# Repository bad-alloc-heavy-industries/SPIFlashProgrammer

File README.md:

# SPI Flash Programmer

After a complete rewrite and re-hash of the original ideal having had it proove itself, a PCB and tightly integrated yet simple to use firmware is the name of the game.

SPIFlashProgrammer is a small but capable board housing a Texas Instruments Tiva-C series ARM microprocessor, two Flash devices for use in a production environment to allow one board to program up to two different target devices on a production line, and USB for power and connecting to a host machine.

When connected to a host, the USB connectivity and `flashprog` utility come together to form a sleak programming experience, allowing the tool to be used in a "set and forget" manner for test and debug of bitstreams and firmware.

## Flash chip support

The firmware targets 25 series memory devices such as the M25P16, W25Q80BV, and AT25SF641.

## Build and installation

Building requires a small number of prerequsites and dependencies:

* [Meson](https://meson.build)
* [Ninja](https://ninja-build.org)
* A modern arm-none-eabi GCC such as the [GNU ARM Embedded Toolchain](https://developer.arm.com/tools-and-software/open-source-software/developer-tools/gnu-toolchain/gnu-rm)
	or any distro or custom build GCC capable of targeting ARMv7 via C++17

To build the firmware and host software, run

```Bash
meson build --cross-file=cross-files/arm-none-eabi.meson
ninja -C build
```

You may then use the results in-place, or install the host software with `ninja -C build install`.

Programming the firmware onto a newly minted board can be achived via any JTAG adapter that can talk TI ICDI.
We use the awesome [Black Magic Probe](https://github.com/blacksphere/blackmagic) with the toolchain GDB.

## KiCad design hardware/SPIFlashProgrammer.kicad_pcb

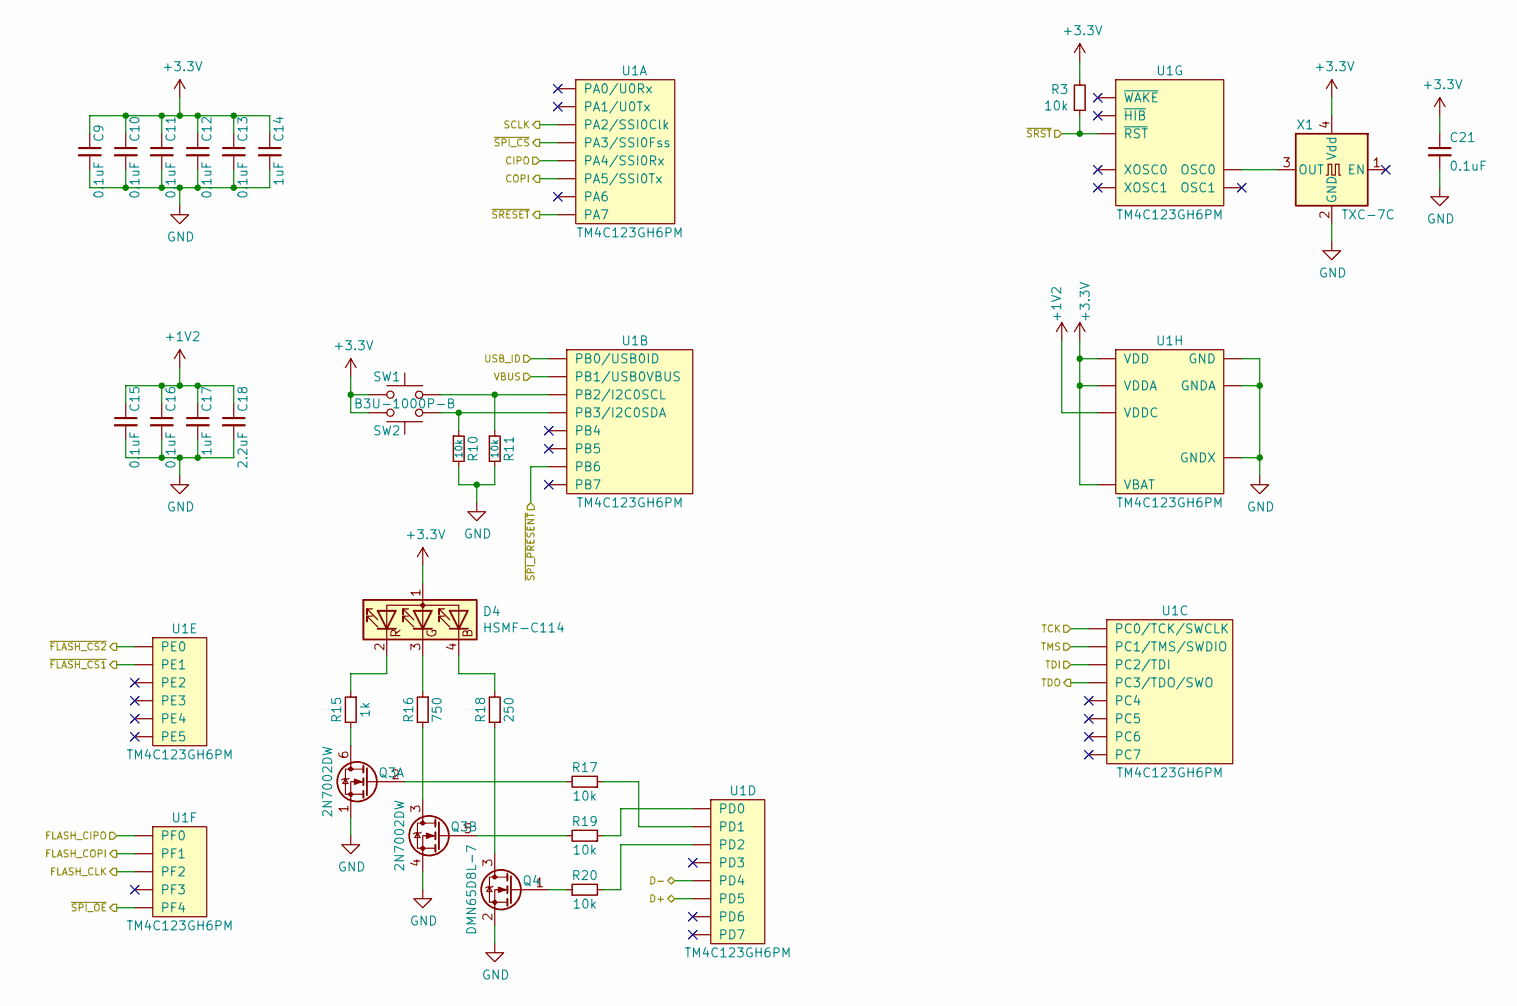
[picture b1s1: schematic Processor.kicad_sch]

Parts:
C9, C10, C11, C12, C13, C15, C16, C21: 0.1uF; C0603; MPN MC0603B104J250CT
C14, C17: 1uF; C0603; MPN MC0603B105K160CT
C18: 2.2uF; C0603; MPN C1608X5R1C225K080AB
D4: HSMF-C114; LED0606; MPN HSMF-C114
Q3: 2N7002DW; SOT-363_SC-70-6; MPN 2N7002DW
Q4: DMN65D8L-7; SOT-23; MPN DMN65D8L-7
R3, R10, R11, R17, R19, R20: 10k; R0603; MPN MC0063W0603110K
R15: 1k; R0603; MPN MC0063W0603110K
R16: 750; R0603; MPN MC0063W0603110K
R18: 250; R0603; MPN MC0063W0603110K
SW1, SW2: B3U-1000P-B; MPN B3U-1000P-B
U1: TM4C123GH6PM; QFP-64_10.2x10.2_Pitch0.5mm; MPN TM4C123GH6PM
X1: TXC-7C; SMD3225; MPN MCSJK-3N-25.00-3.3-50-B

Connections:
+1V2: C15.1, C16.1, C17.1, C18.1, U1.25 (VDDC), U1.56 (VDDC)
+3V3: C9.1, C10.1, C11.1, C12.1, C13.1, C14.1, C21.1, D4.1 (A), R3.2, SW1.1, SW2.1, U1.2 (VDDA), U1.11 (VDD), U1.26 (VDD), U1.37 (VBAT), U1.42 (VDD), U1.54 (VDD), X1.4 (Vdd); also elsewhere on the board
/Connectors/CIPO: U1.21 (PA4/SSI0Rx); also elsewhere on the board
/Connectors/COPI: U1.22 (PA5/SSI0Tx); also elsewhere on the board
/Connectors/D+: U1.44 (PD5); also elsewhere on the board
/Connectors/D-: U1.43 (PD4); also elsewhere on the board
/Connectors/SCLK: U1.19 (PA2/SSI0Clk); also elsewhere on the board
/Connectors/TCK: U1.52 (PC0/TCK/SWCLK); also elsewhere on the board
/Connectors/TDI: U1.50 (PC2/TDI); also elsewhere on the board
/Connectors/TDO: U1.49 (PC3/TDO/SWO); also elsewhere on the board
/Connectors/TMS: U1.51 (PC1/TMS/SWDIO); also elsewhere on the board
/Connectors/USB_ID: U1.45 (PB0/USB0ID); also elsewhere on the board
/Connectors/VBUS: U1.46 (PB1/USB0VBUS); also elsewhere on the board
/Connectors/~SPI_CS: U1.20 (PA3/SSI0Fss); also elsewhere on the board
/Connectors/~SPI_OE: U1.5 (PF4); also elsewhere on the board
/Connectors/~SPI_PRESENT: U1.1 (PB6); also elsewhere on the board
/Connectors/~SRESET: U1.24 (PA7); also elsewhere on the board
/Connectors/~SRST: R3.1, U1.38 (~RST); also elsewhere on the board
/Onboard Flash/CIPO: U1.28 (PF0); also elsewhere on the board
/Onboard Flash/COPI: U1.29 (PF1); also elsewhere on the board
/Onboard Flash/SCK: U1.30 (PF2); also elsewhere on the board
/Onboard Flash/~CS1: U1.8 (PE1); also elsewhere on the board
/Onboard Flash/~CS2: U1.9 (PE0); also elsewhere on the board
GND: C9.2, C10.2, C11.2, C12.2, C13.2, C14.2, C15.2, C16.2, C17.2, C18.2, C21.2, Q3.1 (S), Q3.4 (S), Q4.2 (S), R10.2, R11.2, U1.3 (GNDA), U1.12 (GND), U1.27 (GND), U1.35 (GNDX), U1.39 (GND), U1.55 (GND), X1.2 (GND); also elsewhere on the board
unnamed: D4.2 (RK), R15.1
unnamed: D4.3 (GK), R16.1
unnamed: D4.4 (BK), R18.2
unnamed: Q3.2 (G), R17.2
unnamed: Q3.3 (D), R16.2
unnamed: Q3.5 (G), R19.2
unnamed: Q3.6 (D), R15.2
unnamed: Q4.1 (G), R20.1
unnamed: Q4.3 (D), R18.1
unnamed: R10.1, SW2.2, U1.48 (PB3/I2C0SDA)
unnamed: R11.1, SW1.2, U1.47 (PB2/I2C0SCL)
unnamed: R17.1, U1.62 (PD1)
unnamed: R19.1, U1.61 (PD0)
unnamed: R20.2, U1.63 (PD2)
unnamed: U1.40 (OSC0), X1.3 (OUT)

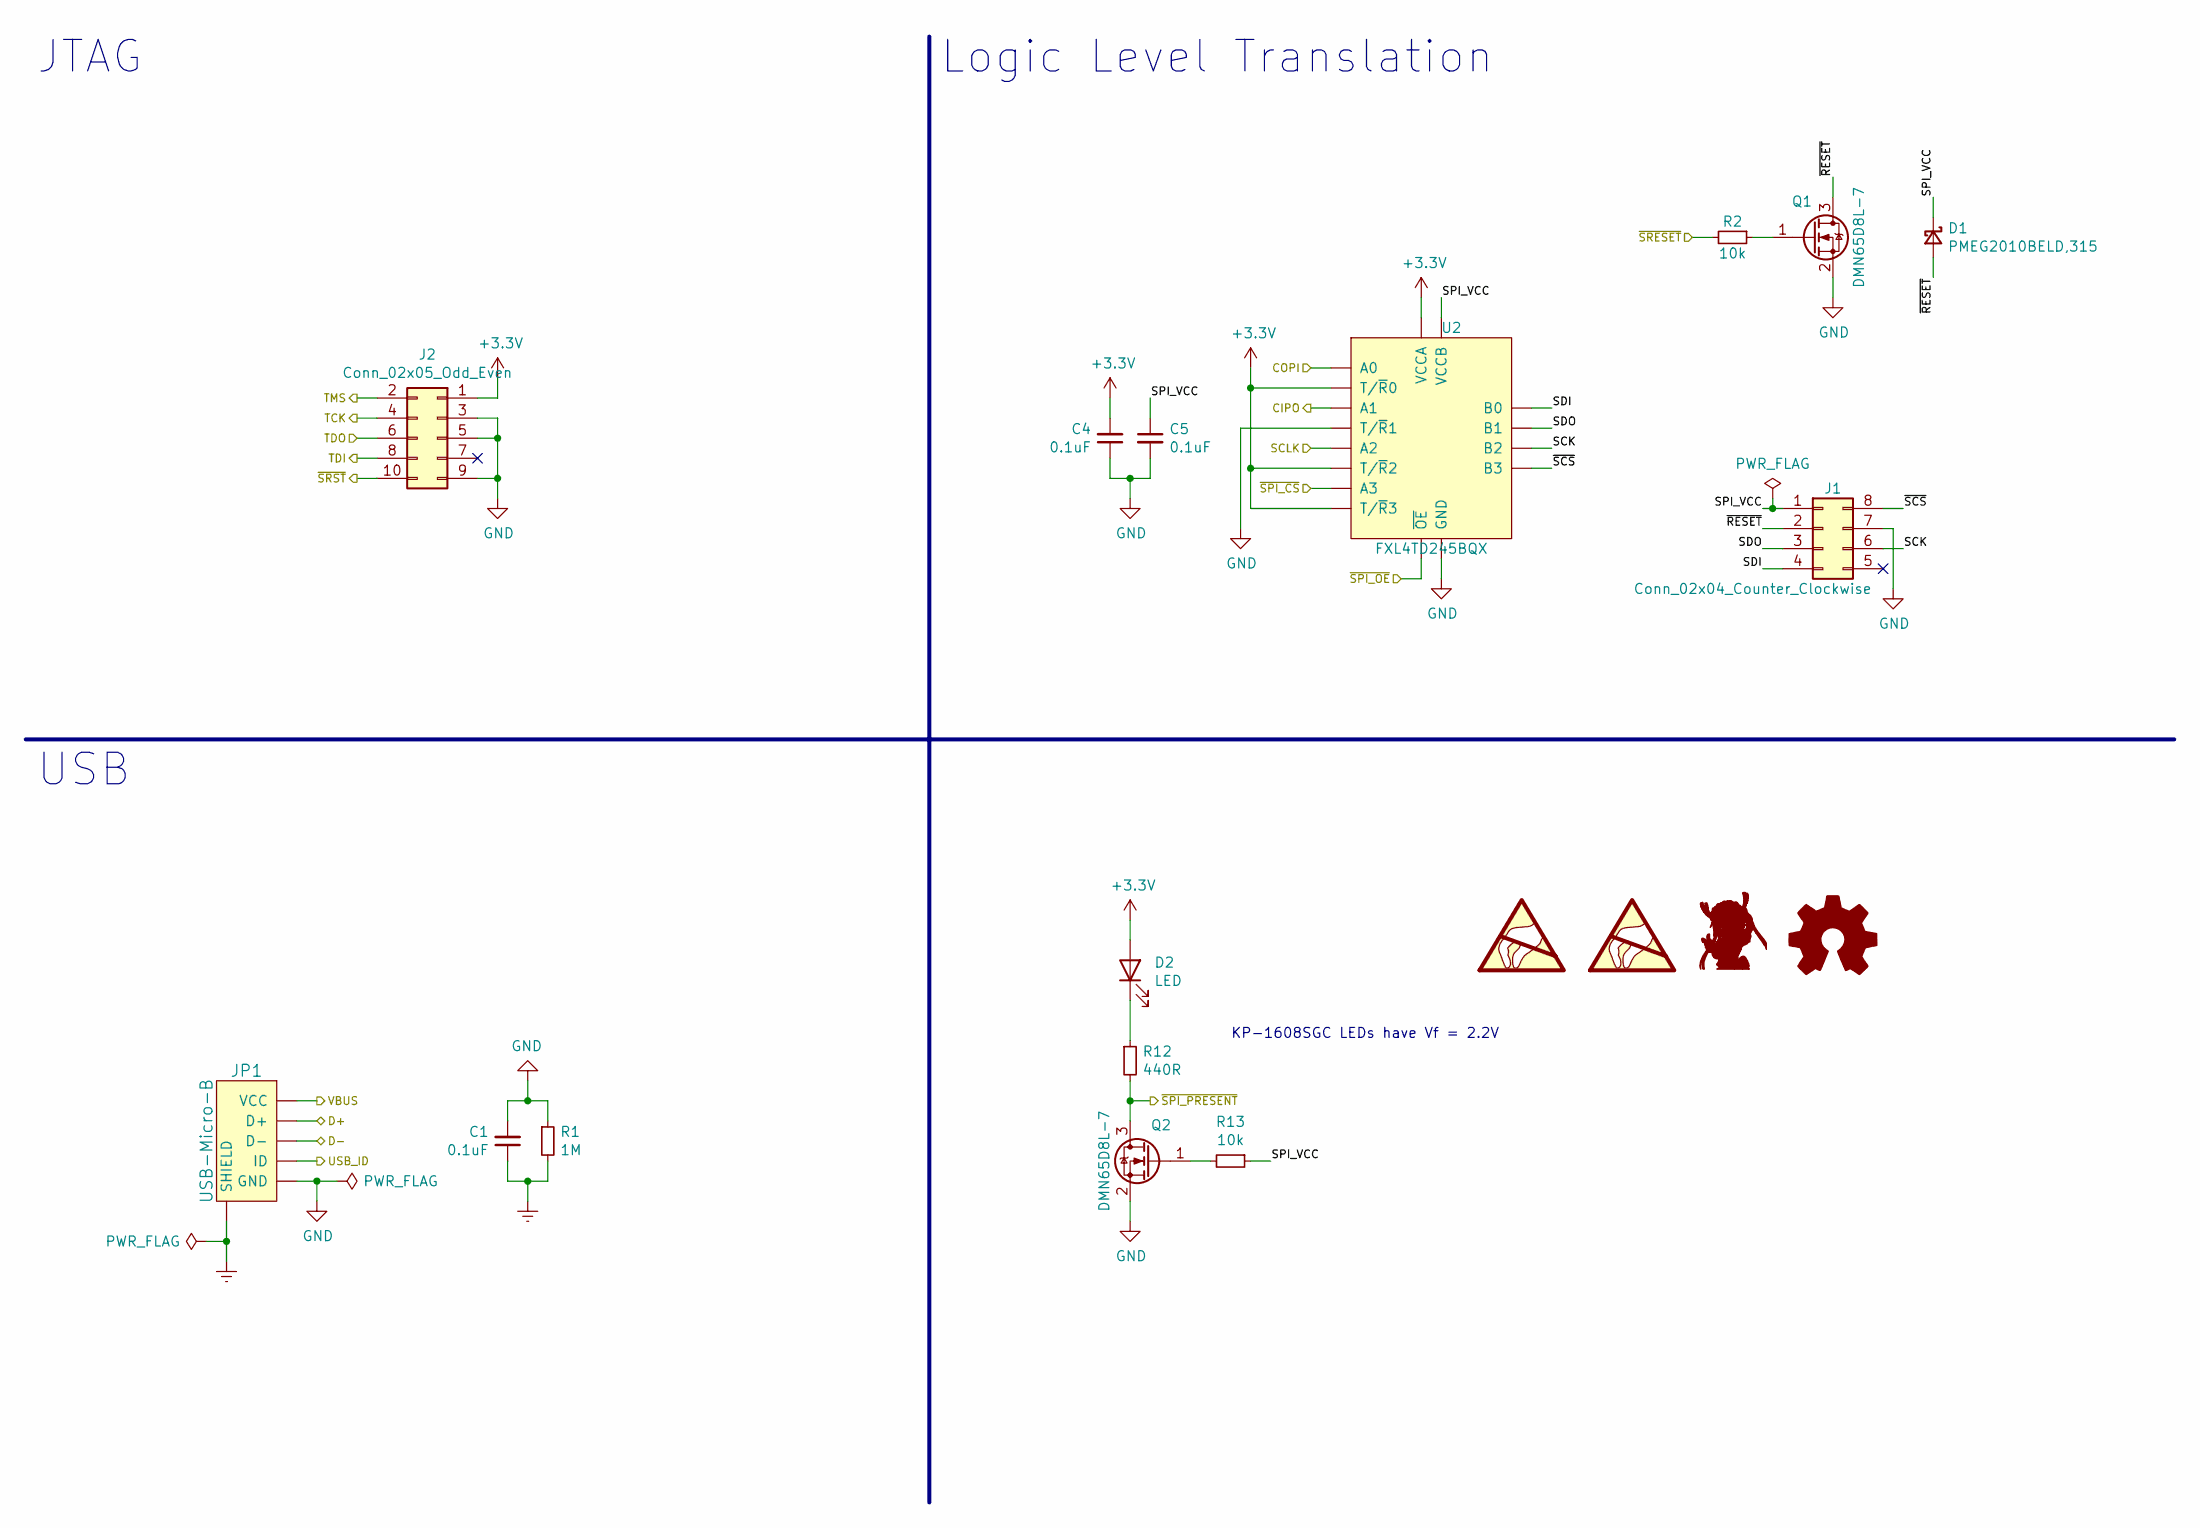
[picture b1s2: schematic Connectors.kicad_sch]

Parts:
C1, C4, C5: 0.1uF; C0603; MPN MC0603B104J250CT
D1: PMEG2010BELD,315; SOD882D_DFN1006D-2; MPN PMEG2010BELD,315
D2: LED; LED0603; MPN KP-1608SGC
DRG1: トール; トール-8.6x9.9
J1: Conn_02x04_Counter_Clockwise; 75867-132LF; MPN 75867-132LF
J2: Conn_02x05_Odd_Even; PinSocket_2x05_P1.27mm_Vertical_SMD; MPN 20021321-00010C4LF
JP1: USB-Micro-B; MICRO-USB-B-(IN_PCB); MPN 10103593-0001LF
LOGO1: Logo_Open_Hardware_Small; OSHW-Symbol_6.7x6mm_SilkScreen
Q1, Q2: DMN65D8L-7; SOT-23; MPN DMN65D8L-7
R1: 1M; R0603; MPN MCWR06X1004FTL
R2, R13: 10k; R0603; MPN MC0063W0603110K
R12: 440R; R0603; MPN MCWR06X4700FTL
SYM1: SYM_ESD_Small; WEEE-Logo_4.2x6mm_SilkScreen
SYM2: SYM_ESD_Small; ESD-Logo_6.6x6mm_SilkScreen
U2: FXL4TD245BQX; DQFN16_1EP_2.5x3.5mm_P0.5mm; MPN FXL4TD245BQX

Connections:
+3V3: C4.2, D2.2 (A), J2.1, U2.1 (VCCA), U2.2 (T/~R0), U2.7 (T/~R3), U2.10 (T/~R2); also elsewhere on the board
/Connectors/CIPO: U2.4 (A1); also elsewhere on the board
/Connectors/COPI: U2.3 (A0); also elsewhere on the board
/Connectors/D+: JP1.D+; also elsewhere on the board
/Connectors/D-: JP1.D-; also elsewhere on the board
/Connectors/SCK: J1.6, U2.12 (B2)
/Connectors/SCLK: U2.5 (A2); also elsewhere on the board
/Connectors/SDI: J1.4, U2.14 (B0)
/Connectors/SDO: J1.3, U2.13 (B1)
/Connectors/SPI_VCC: C5.1, D1.1 (K), J1.1, R13.1, U2.16 (VCCB)
/Connectors/TCK: J2.4; also elsewhere on the board
/Connectors/TDI: J2.8; also elsewhere on the board
/Connectors/TDO: J2.6; also elsewhere on the board
/Connectors/TMS: J2.2; also elsewhere on the board
/Connectors/USB_ID: JP1.ID; also elsewhere on the board
/Connectors/VBUS: JP1.VCC; also elsewhere on the board
/Connectors/~RESET: D1.2 (A), J1.2, Q1.3 (D)
/Connectors/~SCS: J1.8, U2.11 (B3)
/Connectors/~SPI_CS: U2.6 (A3); also elsewhere on the board
/Connectors/~SPI_OE: U2.9 (~OE); also elsewhere on the board
/Connectors/~SPI_PRESENT: Q2.3 (D), R12.2; also elsewhere on the board
/Connectors/~SRESET: R2.2; also elsewhere on the board
/Connectors/~SRST: J2.10; also elsewhere on the board
Earth: C1.1, JP1.SHIELD, R1.2
GND: C1.2, C4.1, C5.2, J1.7, J2.3, J2.5, J2.9, JP1.GND1 (GND), Q1.2 (S), Q2.2 (S), R1.1, U2.8 (GND), U2.15 (T/~R1), U2.EP (GND); also elsewhere on the board
unnamed: D2.1 (K), R12.1
unnamed: Q1.1 (G), R2.1
unnamed: Q2.1 (G), R13.2

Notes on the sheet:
JTAG
USB
KP-1608SGC LEDs have Vf = 2.2V
Logic Level Translation

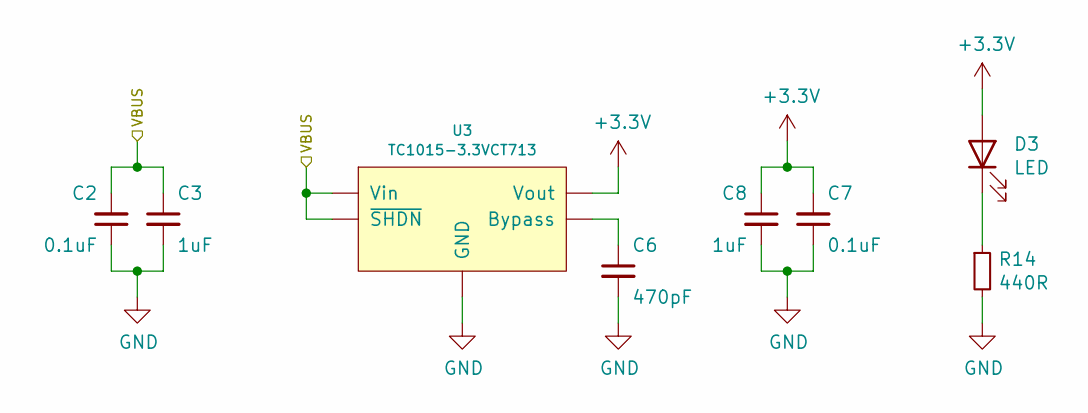
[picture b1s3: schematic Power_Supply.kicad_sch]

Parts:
C2, C7: 0.1uF; C0603; MPN MC0603B104J250CT
C3, C8: 1uF; C0603; MPN MC0603B105K160CT
C6: 470pF; C0603; MPN MC0603B471J500CT
D3: LED; LED0603; MPN KP-1608SGC
R14: 440R; R0603; MPN MCWR06X4700FTL
U3: TC1015-3.3VCT713; SOT-23-5; MPN TC1015-3.3VCT713

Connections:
+3V3: C7.2, C8.1, D3.2 (A), U3.5 (Vout); also elsewhere on the board
/Connectors/VBUS: C2.2, C3.1, U3.1 (Vin), U3.3 (~SHDN); also elsewhere on the board
GND: C2.1, C3.2, C6.2, C7.1, C8.2, R14.2, U3.2 (GND); also elsewhere on the board
unnamed: C6.1, U3.4 (Bypass)
unnamed: D3.1 (K), R14.1

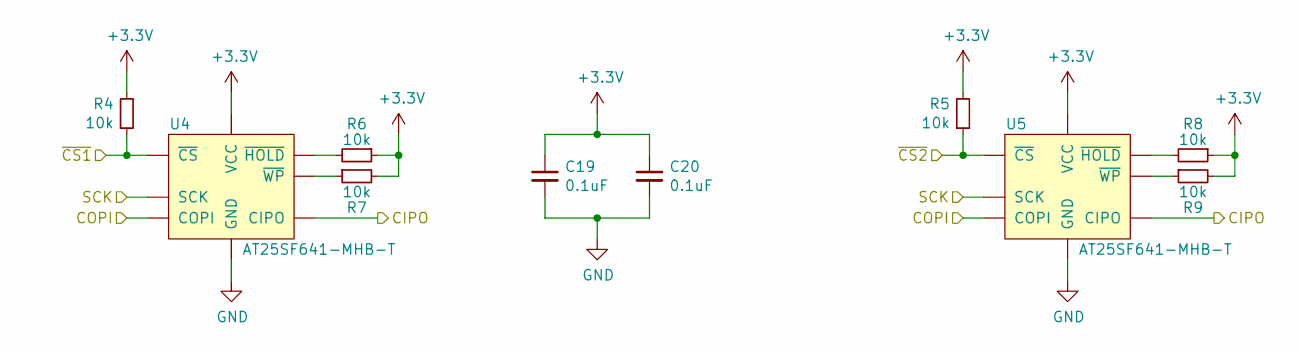
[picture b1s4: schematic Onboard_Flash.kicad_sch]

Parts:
C19, C20: 0.1uF; C0603; MPN MC0603B104J250CT
R4, R5, R6, R7, R8, R9: 10k; R0603; MPN MC0063W0603110K
U4, U5: AT25SF641-MHB-T; UDFN-8-1EP_6x5mm_P1.27mm_EP3.4x4mm; MPN AT25SF641-MHB-T

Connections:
+3V3: C19.1, C20.1, R4.2, R5.2, R6.1, R7.2, R8.1, R9.2, U4.8 (VCC), U5.8 (VCC); also elsewhere on the board
/Onboard Flash/CIPO: U4.2 (CIPO), U5.2 (CIPO); also elsewhere on the board
/Onboard Flash/COPI: U4.5 (COPI), U5.5 (COPI); also elsewhere on the board
/Onboard Flash/SCK: U4.6 (SCK), U5.6 (SCK); also elsewhere on the board
/Onboard Flash/~CS1: R4.1, U4.1 (~CS); also elsewhere on the board
/Onboard Flash/~CS2: R5.1, U5.1 (~CS); also elsewhere on the board
GND: C19.2, C20.2, U4.4 (GND), U4.9 (GND), U5.4 (GND), U5.9 (GND); also elsewhere on the board
unnamed: R6.2, U4.7 (~HOLD)
unnamed: R7.1, U4.3 (~WP)
unnamed: R8.2, U5.7 (~HOLD)
unnamed: R9.1, U5.3 (~WP)

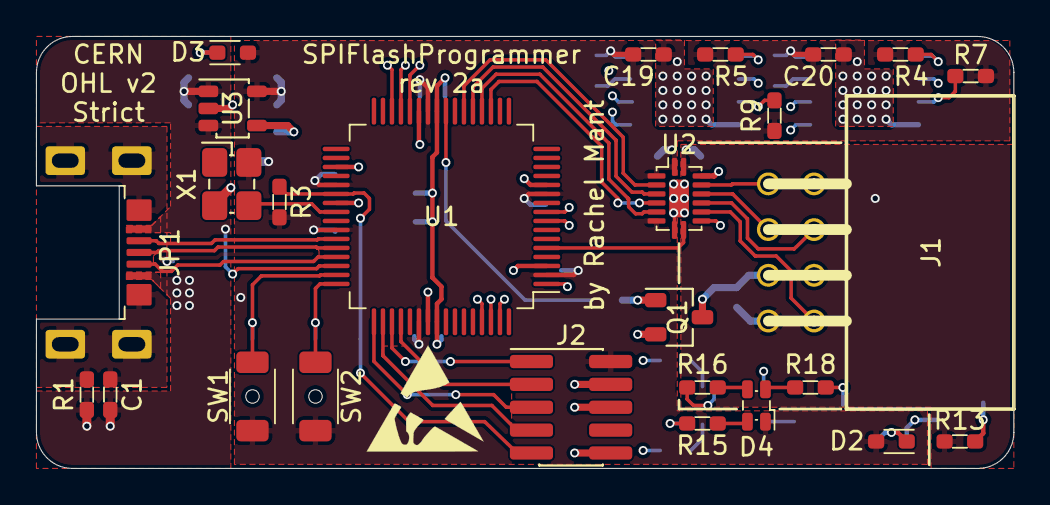
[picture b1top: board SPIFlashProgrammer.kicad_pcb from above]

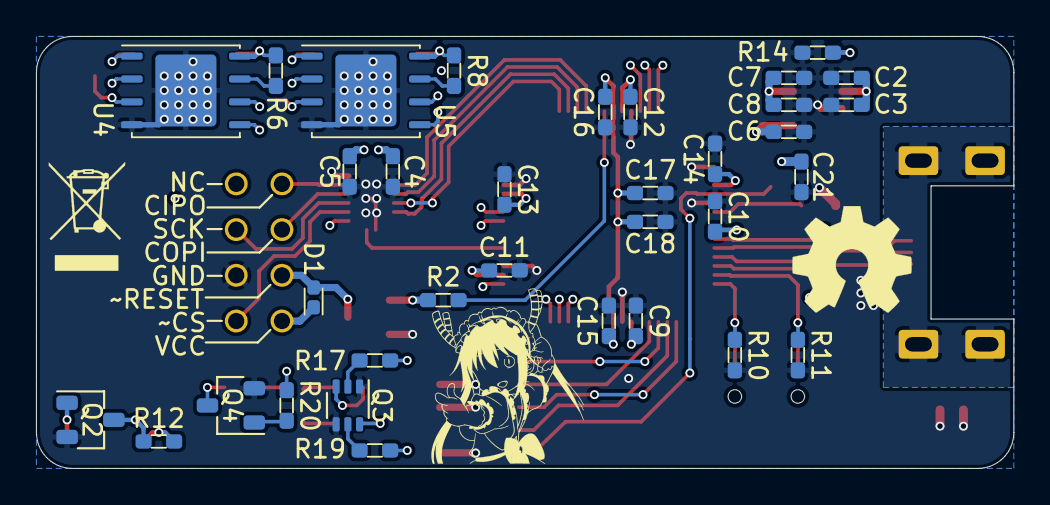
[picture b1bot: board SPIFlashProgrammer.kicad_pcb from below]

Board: 4 copper layers, 54.3 x 24.0 mm, 64 parts (37 on the bottom side), 55 nets.

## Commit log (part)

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2015-03-03 Added a couple more definitions for the LPC port, which for the time being is going no further as it is taking far too long
2015-03-03 Added a device identification system to allow device-specific status and instruction code usage as needed
2020-07-12 Added the schematic and board files from yesterday's stream and the beginnings of v2 of this project
2020-08-30 Updated the parts cache
2020-08-30 Made some decent progress on the Saturday livestream routing the board
2020-10-04 Updated the board with the work done on the last stream
2020-10-18 Added the two Flash devices and the user buttons to the schematic
2020-10-21 Added the power LED for the target I missed
2020-10-21 Updated the schematic symbol cache
2020-10-21 Fixed some DRC and polygon poor problems
2020-10-26 Updates to the symbol library cache for ERC
2020-10-30 Fixed the choice of license, switching from CERN OHL v1.2 to v2 Strict
2020-11-07 Updated the logic level translator to include the fab layer drawing
2020-11-08 Moved SPIFlashProgrammer v1's firmware and interface program out of the way to make way for SPIFlashProgrammer rev 2
2020-11-10 Wrote a platform header based on the SVD for the chip, and implemented LED init code
2020-11-10 Cleaned up the constants header and cleaned up the include tree
2020-11-11 Implemented on-board SPI bus controller bring-up
2020-11-11 Implemented the internal flash read/write SPI routines
2020-11-11 Implemented a simple RGB LED colour selector function
2020-11-14 Fixed the SPI bus bring-up problems on PortF
2020-11-14 Begun cleaning up the old TivaC firmware
2020-11-14 Added the Contributors Covenant Code of Conduct to the repo
2020-11-15 stubbed in support for USB
2020-11-16 Implemented the bulk of port set-up for USB
2020-11-16 Implemented suspend, resume, and further parts of the stack initialisation for USB
2020-11-17 Moved the endpoint direction type into a more sensible location in the headers
2020-11-17 Cleanup and added some missing types to the USB types header
2020-11-17 Implemented support for the setup packet request types
2020-11-17 Started fleshing out usbServiceCtrlEPComplete()
2020-11-18 noexcept-correctness and made use of the new functionality
2020-11-21 Cleanup in the device driver
2020-11-21 Implemented some more of the EP0 setup packet handling
2020-12-05 Refactoring for the USB Standard Request handler
2020-12-06 Added notes on how the USB peripheral works
2020-12-06 Fixed some issues with missing brackets around bitwise and boolean operations
2020-12-06 Fixed an ODR violation
2020-12-07 Removed some more chunks of the old firmware now we don't need them any more
2020-12-09 Added support to usbEPStatus_t for multi-part responses
2020-12-09 Created some sanity for how sendCount is being calculated so codegen can be more optimal
2020-12-09 Fixed some issues with interrupt handling in the base USB driver
2020-12-11 Fixed some issues with the multi-part packet handling
2020-12-13 Moved the USB core variables into a proper USB core header, and moved out sendData() and recvData() properly
2020-12-21 Added support for sending back a device qualifier descriptor
2021-01-14 Fixed a couple of errors in the linker script for the platform
2021-02-06 Added in some logic to properly truncate answers to the requested length
2021-02-06 Added support for automatically programming SPIFlashProgrammer from a built firmware blob
2021-02-06 Respond to but don't action set configuration requests so USB bringup is complete/works
2021-02-09 Renamed the USB peripheral MMIO variable in the platform header to allow the namespaces situation to be cleaned up
2021-02-09 Begun implementing handleSetConfiguration and cleaned up the usbResetEPs() call scheme
2021-02-13 Done a little reorganisation
2021-02-13 Bring libusb into conformance as best as possible, and turn off the resulting warnings
2021-02-14 Implemented support for the set configuration control request
2021-02-14 Fixed a bug in the usb::device::setupEndpoint() logic that would have cause it to malfunction for EP2, etc
2021-02-14 Implemented usb::core::readEP()
2021-02-14 Begun implementing the USB <-> Flash protocol in the firmware
2021-02-14 Cleaned up some loose whitespace in the onboard Flash schematic sheet
2021-02-18 Reordered things in the build system to make a little more sense
2021-02-18 Added entry into normal sleep ('wait for interrupt') to the main loop of the firmware
2021-02-21 Added versioning information for the PC utility
2021-02-21 Implemented the args parser for flashprog and the first argument handling
    The arguments so far are help and version + some of the logic for the programming commands
2021-02-22 Implemented most of usb::device::handleGetStatus()
2021-03-13 Fixed the logic in usb::device::setupEndpoint
2021-03-13 Fixed a couple of small issues with the flashProto code that was causing garbage to happen
2021-03-14 Implemented argChip_t for the PC software
2021-03-14 Implemented listing the flash chips attached to a SPI Flash Programmer
2021-03-14 Cleaned up usb::flashProto::handleDeviceCount()
2021-03-14 Begun implementing usb::flashProto::handleTargetDevice()
2021-04-10 Fixed some missing ""sv annotations
2021-04-10 Cleaned up the firmware side of the response handling
2021-04-11 Implemented argFile_t
2021-04-11 Implemented a function to check if there's space in an endpoint's TX FIFO
2021-04-21 Added LGTM build rules for the project
2021-05-01 Fixed a signed-unsigned comparison
2021-05-08 Sending the device qualifier descriptor as a full-speed USB 2.0 device is not spec-compliant
2021-05-08 KiCad file updates
2021-06-05 Fixed some missing default initialisation for setupPacket_t and a namespace comment
2021-06-05 Fixed the lack of error checking in the readDevice() logic in the PC software
2021-06-05 Switched the flashProto request and response buffers to use uint8_t for use simplicity
2021-06-05 Moved the setting of the memory buffer for sendResponse() into sendResponse() in flashProto
2021-06-05 Improved the error reporting in the libusb wrapper interrupt transfer routine
2021-06-19 Changed the way the progress spinner is done to use time rather than the count changing
2021-06-19 Switched substrate to not build tests by default
2021-06-19 Moved to using the dragonTI version of the Tiva-C headers
2021-06-20 Switched from our own copy of the USB stack to the one in dragonUSB
2021-06-22 Updated the USB Flash protocol driver to work with the latest dragonUSB
2021-06-22 Moved the handler registration into the flashProto driver for cleanliness
2021-06-23 Added parameters to usb::flashProto::registerHandlers() for registring dynamically to endpoints in given configurations
2021-06-26 Added DFU driver registration to the startup code
2021-06-30 Switched the flashProto driver to using usb::core::readEPDataAvail() now the hack "fix" has gone away
2021-07-01 Cleaned up the bulk of the remaining old flashprog/firmware code
2021-07-16 Fixed some small details taht changed with the most recent dragonUSB or were just wrong in flashProto.cxx
2021-09-29 Implemented control transfer support on our libusb usbDeviceHandle_t adaptor type
2021-09-29 Switched messages_t::listDevice to the new protocol
2021-09-29 Cleaned up in usbProtocol.hxx after restructuring the protocol
2021-09-29 Fixed a typo in the control transfer failure error message
2021-09-29 Finished cleaning up usages of requests::listDevice_t
2021-09-29 Added support for bulk transfers to usbDeviceHandle_t
2021-09-29 Added a read count to the read_t request
2021-09-29 Added some extra error checking to usb::flashProto::handleCtrlRequest()
2021-09-30 Fixed the zero-size array warnings from the DFU driver
2021-10-02 Updated the cross-files to reflect our current compilation environments
2021-10-09 Rewrote the erase component of the protocol using EP0 for control
2021-10-09 Rewrote the write component of the protocol to use EP0 for control and EP1 Out for bulk data
2021-10-09 Added an abort message, ready for later implementation
2021-11-26 Cleaned up the code gen of a couple of irq functions
2021-11-26 Implemented an easy chip identification call for the SPI Flash devices
2021-11-26 Done a first pass at detecting externally plugged in Flash
2022-01-01 Added a flash chip database to the firmware to help with the page size and capacity detection issues
2022-02-13 Added the GigaDevice GD25Q40C to the chip table
2022-02-13 Added support for waking the target device if it's in deep sleep when trying to ID it
2022-02-13 Upgraded the flashprog command line interface so which bus (int/ext) the chip you want to poke is on can be specified
2022-02-13 Updated the chip number validation message
2022-02-13 Updated writeDevice() so it can work with external chip targets
2022-02-14 Fixed part of the erase logic as it was issuing incorrect erase addresses
2022-02-14 Implemented device deselection into the PC tool
2022-02-14 Fixed handleTargetDevice() not allowing device deselection
2022-02-15 Implemented the resetTarget message handler in the firmware
2022-02-16 Upgraded the KiCad files to v6 format
2022-02-16 Added control for the level shifter output enable to the CPU to fix problems caused by us accidentally still driving the external bus after reset is released
2022-02-16 Upgraded the help the flashprog utility prints with `-h`
2022-02-18 Patched performRead() to work correctly with the W25N01GV
2022-04-17 Added a couple new Flash chips to the chip DB
2022-04-17 Fixed a logic error that had 16MiB chips reading and writing wrong
2022-08-05 Created a rough and ready implementation of the SFDP spec for the firmware
2023-02-04 Implemented display of the Flash chip size information when reading and writing
2023-02-04 Implemented a structure for creating and sending abort commands to the firmware
2023-02-05 Turn off the clang-tidy lint ono confusable parameters as there's not much we can do about that
2023-02-05 CXC compiler settings upgrade
2023-02-05 Added more comments to the firmware USB protocol read handler so it's harder to get lost in the code
2023-02-05 Code style and clang-tidy cleanup in the firmware USB protocol implementation
2023-02-05 Fixed lots of clang-tidy lints in the libusb wrappers
2023-02-05 Refactored writeDevice() in flashprog a bit to reduce complexity and improve readability
2023-02-05 Improved the naming of the progress bar variables in flashprog
2023-02-05 Fixed some clang-tidy lints in the SPI abstractions of the firmware
2023-02-06 Added a wrap for lib{fmt}
2023-02-06 Documented the progress bar builder
2023-02-06 Prepared flash::findChip() for calling into the SFDP reader and making use of the information returned
2023-02-06 Cleaned up the "listDevices" output slightly so it's a little less confusing when no extenal devices are attached
2023-02-06 Implemented firmware protocol support for being able to perform arbitrary SFDP data block reads on any attached Flash chips
2023-02-06 Implemented display of the SFDP header block
2023-02-06 Begun implementing support for the Basic Parameter Table block in flashprog's SFDP reader
2023-02-06 Switched about the SFDP Basic Parameter Table display to be a little more useful for the opcodes shown
2023-02-07 Added some basic indications with the RGB LED as to where the firmware is in the communications process
2023-02-07 Fixed the exponetiation issue for the SFDP capacity value with an integral log2() implementation
2023-05-14 Cleaned up the gerber file situation in the hardware
